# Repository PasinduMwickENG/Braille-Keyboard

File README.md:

# Braille Keyboard – Custom HID Device for Typing & Media Control

A **custom Braille keyboard** built on ESP32 with USB HID support. This project allows users to type using Braille input, control media, and program custom macros directly via USB. It’s designed for accessibility, efficiency, and modular hardware customization.  

---

## 🛠 Features

- **Braille Input**  
  - Type letters, numbers, and punctuation using a 6-dot Braille system.  
  - Supports capitalization and numeric input modifiers.  

- **Secondary Numpad**  
  - Direct number input using a 6-button pad.  

- **Custom Keys**  
  - 3 programmable keys for macros.  
  - 3 media/control keys (volume, play/pause, next/previous).  
  - Multiple custom modes (Media, Modifiers, Programming).  

- **Special Keys**  
  - Dedicated Backspace, Enter, Space, Delete, and Caps Lock keys.  

- **Programming Mode**  
  - Easy macro programming stored in EEPROM.  

- **Robust USB HID Implementation**  
  - Works with both keyboards and consumer control (media) devices.  

---

## 🔧 Hardware Overview

### Pin Configuration

| Function | Pins |
|----------|------|
| Braille Input | 6, 5, 4, 7, 15, 16 |
| Numpad Input | 8, 18, 17, 9, 10, 11 |
| Custom Keys | 12, 13, 14, 20, 45, 3 |
| Special Keys | SPACE: 38, ENTER: 42, BACKSPACE: 37, DELETE: 39, CAPSLOCK: 21 |
| Mode & Programming | MODE: 41, PROGRAM: 2, CUSTOM_MAIN: 46 |

---

### Hardware Components

- ESP32 microcontroller (any variant supporting USB HID)  
- Tactile push buttons for Braille input  
- Numpad buttons for secondary input  
- Custom/macro keys  
- Enclosure with key alignment and ergonomic layout  

---

## 🖥 PCB & Enclosure

### PCB Design

- Designed with KiCAD  
- 2-layer PCB supporting all input buttons and USB HID interface  
- Optimized for compact Braille keyboard layout

### Enclosure

- 3D-printed  enclosure  
- Ergonomic key placement for Braille typing  
- Openings for USB and buttons  

---

## 💻 Software

### Libraries Used

- `USB.h` – USB core for ESP32 HID support  
- `USBHIDKeyboard.h` – Keyboard HID functions  
- `USBHIDConsumerControl.h` – Media/Consumer control HID  
- `EEPROM.h` – Store programmed macros  
- `esp_system.h` – System-level operations  

### Features

- Robust Braille mapping with letters and punctuation  
- Customizable macros via programming mode  
- Support for both media keys and modifier shortcuts  
- EEPROM storage to retain macros across power cycles  

### Usage

1. Connect the ESP32 to your PC via USB.  
2. Input letters using the Braille keys.  
3. Switch modes using the **Mode** button.  
4. Program macros using the **Program** button in Custom Mode 2.  

---

## 📝 Code Structure

- `setup()` – Initializes USB HID, EEPROM, and pins  
- `loop()` – Main logic for Braille input, numpad, custom keys, and special keys  
- `getBraille()` – Maps Braille patterns to letters/punctuation  
- `sendShortcut()` – Sends Ctrl-based keyboard shortcuts  
- `sendMedia()` – Sends media control codes  

---

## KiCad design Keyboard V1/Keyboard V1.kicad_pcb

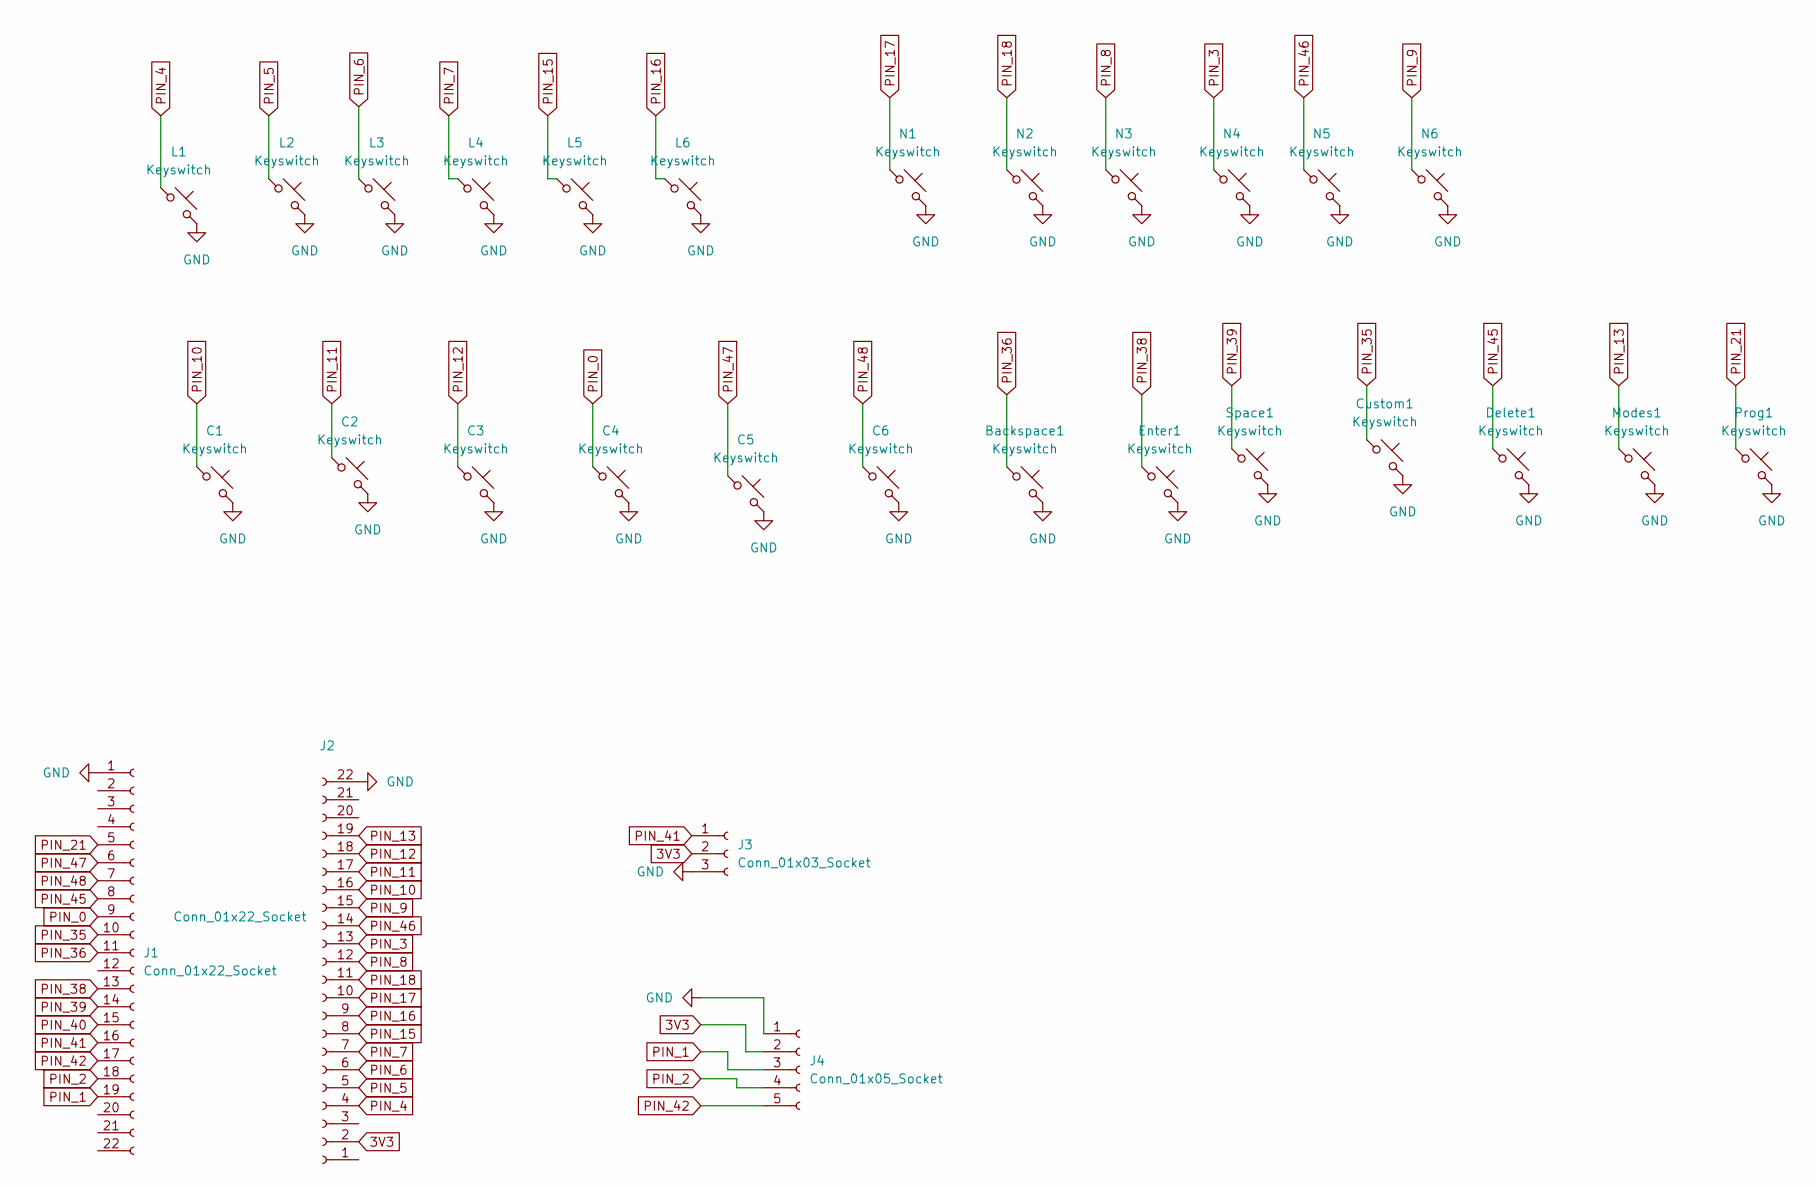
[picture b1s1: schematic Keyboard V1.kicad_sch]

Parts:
Backspace1: Keyswitch; MX_PCB_1.00u
C1, C2, C3, C4, C5, C6: Keyswitch; MX_PCB_1.00u
Custom1: Keyswitch; MX_PCB_1.00u
Delete1: Keyswitch; MX_PCB_1.00u
Enter1: Keyswitch; MX_PCB_1.00u
J1, J2: Conn_01x22_Socket; PinSocket_1x22_P2.54mm_Vertical
J3: Conn_01x03_Socket; PinSocket_1x03_P2.54mm_Vertical
J4: Conn_01x05_Socket; PinSocket_1x05_P2.54mm_Vertical
L1, L2, L3, L4, L5, L6: Keyswitch; MX_PCB_1.00u
Modes1: Keyswitch; MX_PCB_1.00u
N1, N2, N3, N4, N5, N6: Keyswitch; MX_PCB_1.00u
Prog1: Keyswitch; MX_PCB_1.00u
Space1: Keyswitch; MX_PCB_1.00u

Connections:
3V3: J2.2, J3.2, J4.2
GND: Backspace1.2, C1.2, C2.2, C3.2, C4.2, C5.2, C6.2, Custom1.2, Delete1.2, Enter1.2, J1.1, J2.22, J3.3, J4.1, L1.2, L2.2, L3.2, L4.2, L5.2, L6.2, Modes1.2, N1.2, N2.2, N3.2, N4.2, N5.2, N6.2, Prog1.2, Space1.2
PIN_0: C4.1, J1.9
PIN_1: J1.19, J4.3
PIN_2: J1.18, J4.4
PIN_3: J2.13, N4.1
PIN_4: J2.4, L1.1
PIN_5: J2.5, L2.1
PIN_6: J2.6, L3.1
PIN_7: J2.7, L4.1
PIN_8: J2.12, N3.1
PIN_9: J2.15, N6.1
PIN_10: C1.1, J2.16
PIN_11: C2.1, J2.17
PIN_12: C3.1, J2.18
PIN_13: J2.19, Modes1.1
PIN_15: J2.8, L5.1
PIN_16: J2.9, L6.1
PIN_17: J2.10, N1.1
PIN_18: J2.11, N2.1
PIN_21: J1.5, Prog1.1
PIN_35: Custom1.1, J1.10
PIN_36: Backspace1.1, J1.11
PIN_38: Enter1.1, J1.13
PIN_39: J1.14, Space1.1
PIN_40: J1.15
PIN_41: J1.16, J3.1
PIN_42: J1.17, J4.5
PIN_45: Delete1.1, J1.8
PIN_46: J2.14, N5.1
PIN_47: C5.1, J1.6
PIN_48: C6.1, J1.7

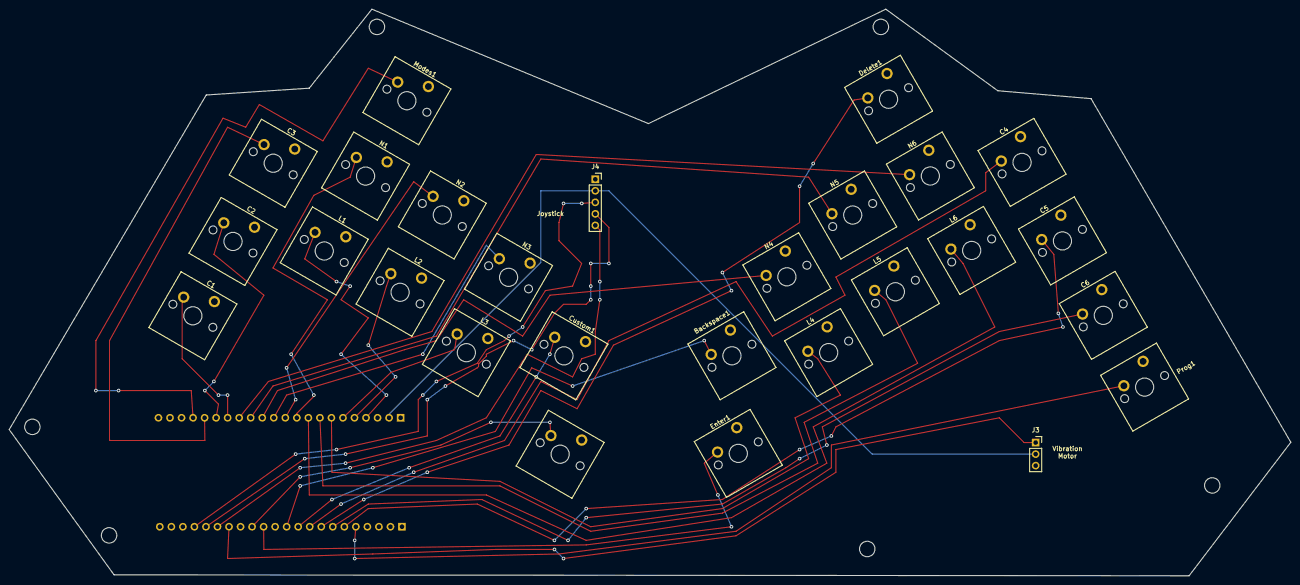
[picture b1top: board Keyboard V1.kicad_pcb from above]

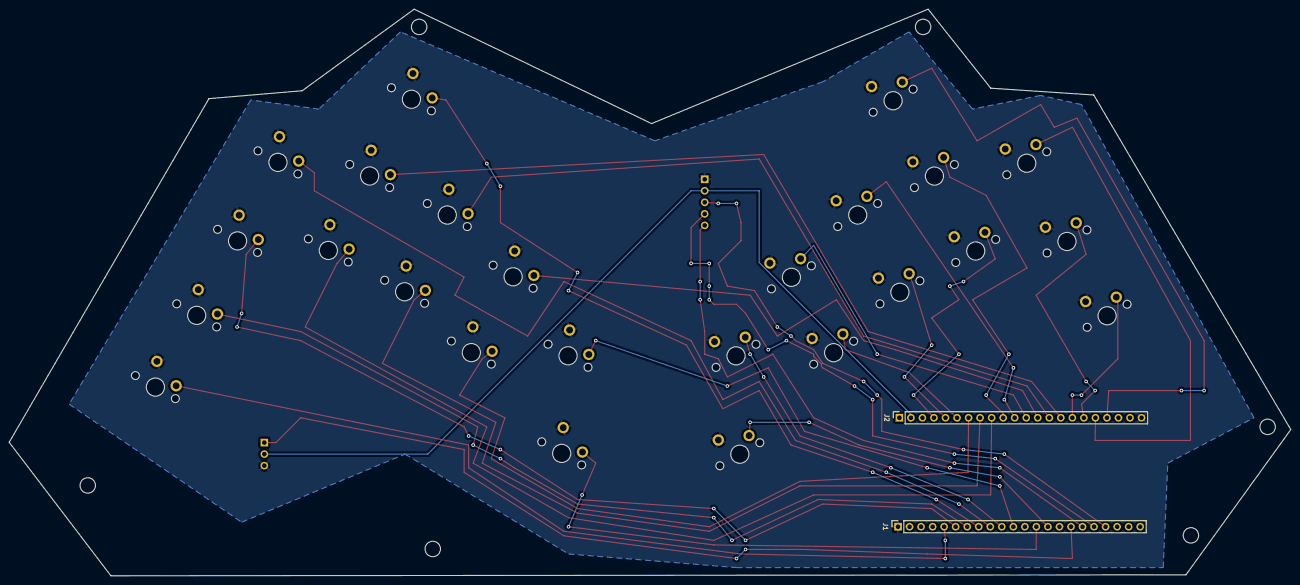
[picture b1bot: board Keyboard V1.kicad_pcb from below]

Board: 4 copper layers, 282.3 x 124.8 mm, 29 parts (2 on the bottom side), 31 nets.

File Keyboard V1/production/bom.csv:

Designator,Footprint,Quantity,Value,LCSC Part #
"BACKSPACE1, C1, C2, C3, C4, C5, C6, CUSTOM1, DELETE1, ENTER1, L1, L2, L3, L4, L5, L6, MODES1, N1, N2, N3, N4, N5, N6, PROG1, SPACE1",MX_PCB_1.00u,25,Keyswitch,
"J1, J2",PinSocket_1x22_P2.54mm_Vertical,2,Conn_01x22_Socket,
J3,PinSocket_1x03_P2.54mm_Vertical,1,Conn_01x03_Socket,
J4,PinSocket_1x05_P2.54mm_Vertical,1,Conn_01x05_Socket,
